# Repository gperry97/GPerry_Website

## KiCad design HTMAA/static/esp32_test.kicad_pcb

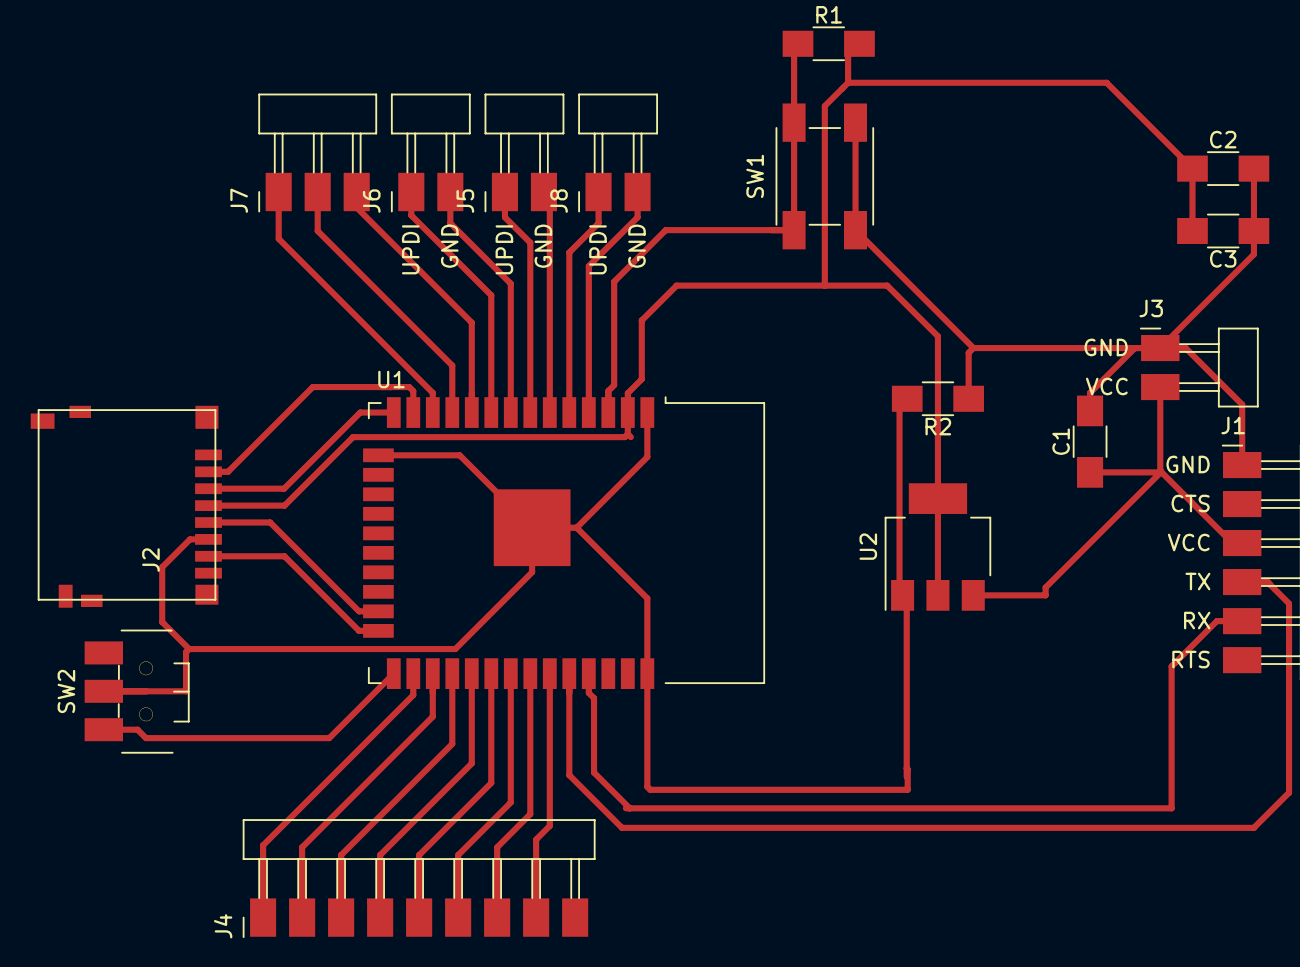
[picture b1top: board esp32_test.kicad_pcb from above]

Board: 2 copper layers, 17 parts (0 on the bottom side), 27 nets.

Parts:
C1, C2, C3: C; C_1206
J1: Conn_PinHeader_FTDI_1x06_P2.54mm_Horizontal_SMD; PinHeader_FTDI_01x06_P2.54mm_Horizontal_SMD
J2: Micro_SD_Socket; MicroSD_Amphenol_114-00841-68
J3, J5, J6, J8: Conn_PinHeader_1x02_P2.54mm_Horizontal_SMD; PinHeader_UPDI_01x02_P2.54mm_Horizontal_SMD
J4: Conn_PinHeader_1x09_P2.54mm_Horizontal_SMD; PinHeader_1x09_P2.54mm_Horizontal_SMD
J7: Conn_PinHeader_1x03_P2.54mm_Horizontal_SMD; PinHeader_1x03_P2.54mm_Horizontal_SMD
R1, R2: R; R_1206
SW1: BUTTON_B3SN; Button_Omron_B3SN_6x6mm
SW2: SWITCH_AYZ0102AGRLC; Switch_SPDT_C&K_AYZ0102AGRLC_7.2x3mm_P2.5mm
U1: Radio_ESP32-WROOM-32E; ESP32-WROOM-32E
U2: Regulator_Linear_ZLDO1117-3.3V-1A; SOT-223-3_TabPin2

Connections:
GND: C1.2, C2.2, C3.1, J1.1, J2.6, J3.1, R2.1, R2.2, SW1.2, SW2.2, U1.1, U1.15, U1.38, U1.39, U2.1
unnamed: C1.1, J1.3, J3.2, U2.3
unnamed: J1.4, U1.34
unnamed: J1.5, U1.35
unnamed: J2.2, U1.13
unnamed: J2.3, U1.14
unnamed: J2.5, U1.23
unnamed: J2.7, U1.24
unnamed: J4.1, U1.26
unnamed: J4.2, U1.27
unnamed: J4.3, U1.28
unnamed: J4.4, U1.29
unnamed: J4.5, U1.30
unnamed: J4.6, U1.31
unnamed: J4.8, U1.33
unnamed: J5.1, U1.7
unnamed: J5.2, U1.6
unnamed: J6.1, U1.9
unnamed: J6.2, U1.8
unnamed: J7.1, U1.12
unnamed: J7.2, U1.11
unnamed: J7.3, U1.10
unnamed: J8.1, U1.5
unnamed: J8.2, U1.4
unnamed: R1.1, SW1.1, U1.3
unnamed: SW2.1, U1.25
VDD: C2.1, C3.2, J2.4, R1.2, U1.2, U2.2

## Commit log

2021-01-05 Create CNAME
2022-01-10 HTMAA Update + cleaning
2022-01-12 Unveil Update
2022-10-31 Fixing website tabs
2022-12-15 Resume Update 12.14.2022
2022-12-15 updateagain
2022-12-29 updates 12.29 4:36
2022-12-30 Crochet Updates + About Words
2022-12-30 crochet edits
2022-12-30 fix crochet links
